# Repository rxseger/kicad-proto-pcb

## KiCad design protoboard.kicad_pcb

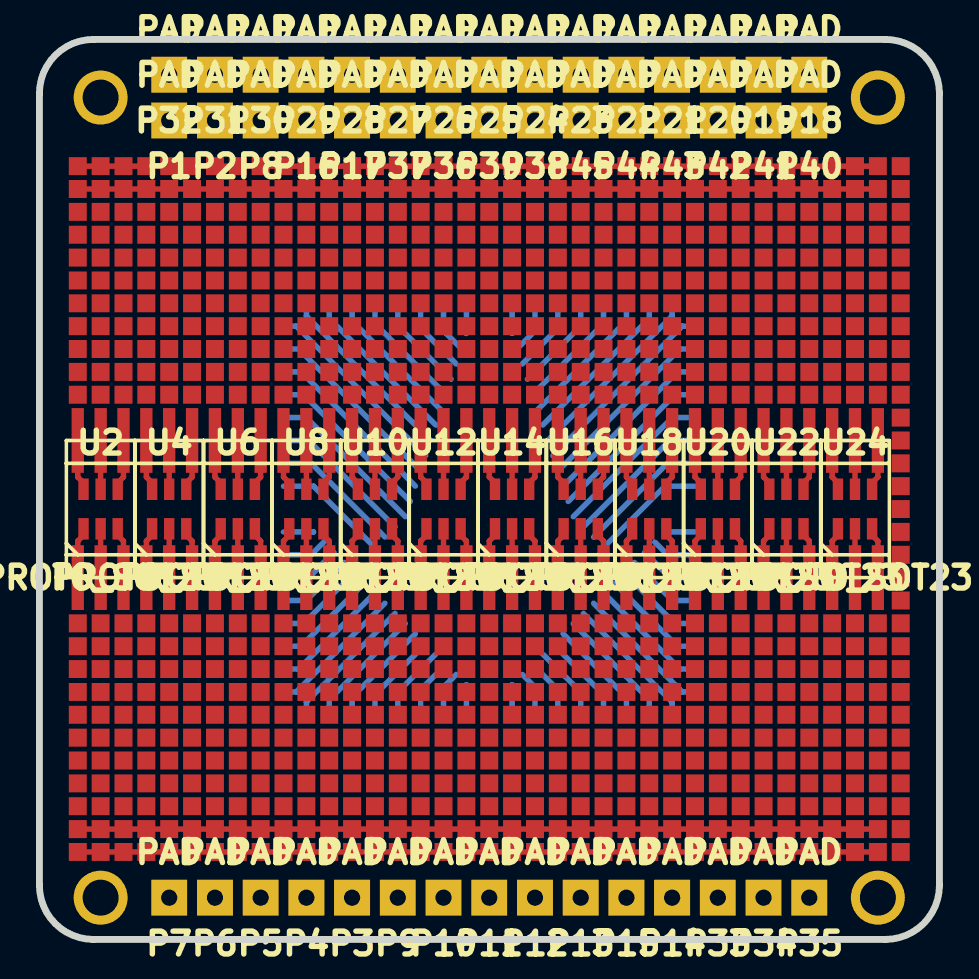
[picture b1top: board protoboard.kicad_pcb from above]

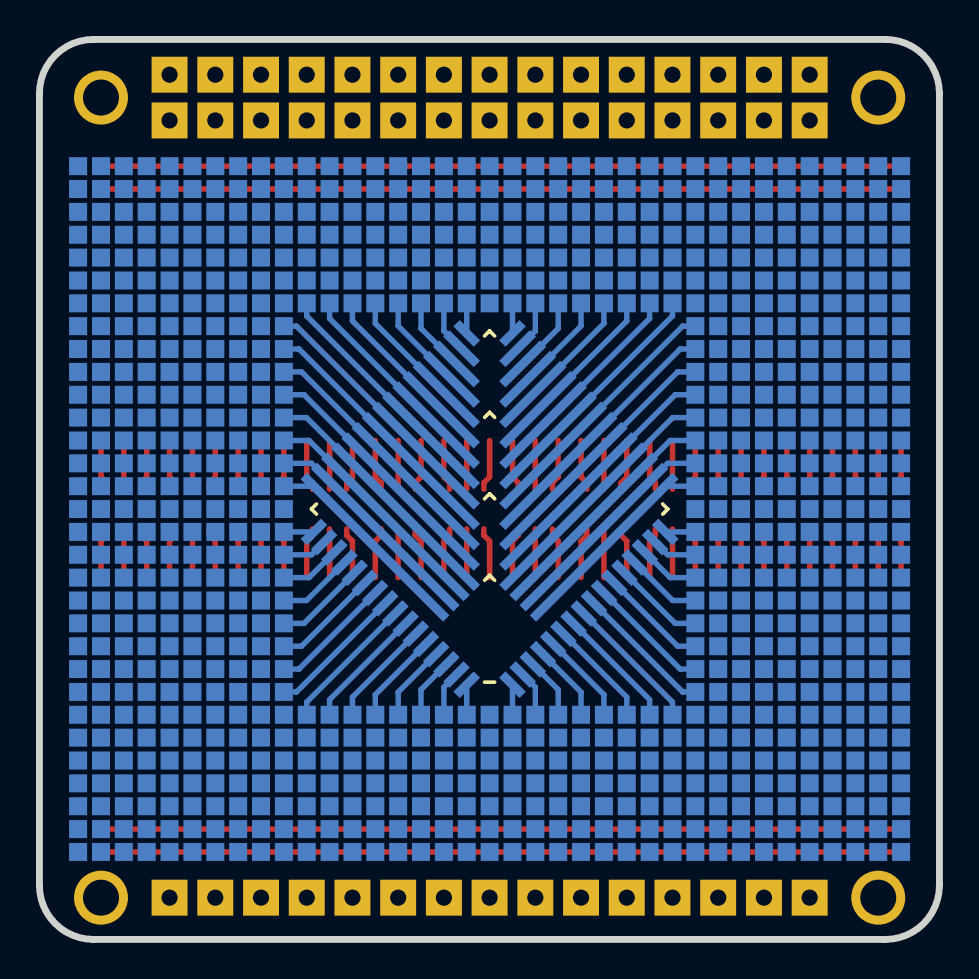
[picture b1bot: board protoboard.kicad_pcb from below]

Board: 2 copper layers, 50.0 x 50.0 mm, 1755 parts (859 on the bottom side), 140 nets.

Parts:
H1, H2, H3, H4: HOLE; hole_2mm
P1, P2, P3, P4, P5, P6, P7, P8, P9, P10, P11, P12, P13, P14, P15, P16, P17, P18, P19, P20, P21, P22, P23, P24, P25, P26, P27, P28, P29, P30, P31, P32, P33, P34, P35, P36, P37, P38, P39, P40, P41, P42, P43, P44, P45: PAD; proto_pad2
PT1, PT2, PT3, PT4, PT5, PT6, PT7, PT8, PT9, PT10, PT11, PT12, PT13, PT14, PT15, PT16, PT17, PT18, PT19, PT20, PT21, PT22, PT23, PT24, PT25, PT26, PT27, PT28, PT29, PT30, PT31, PT32, PT33, PT34, PT35, PT36, PT37, PT38, PT39, PT40, PT41, PT42, PT43, PT44, PT45, PT46, PT47, PT48, PT49, PT50, PT51, PT52, PT53, PT54, PT55, PT56, PT57, PT58, PT59, PT60, PT61, PT62, PT63, PT64: PAD; proto_pad
TQFP1: PROTO_TQFP64; proto_tqfp_08
U1, U3, U5, U7, U9, U11, U13, U15, U17, U19, U21, U23: PROTO_SOIC6; proto_soic6
U2, U4, U6, U8, U10, U12, U14, U16, U18, U20, U22, U24: PROTO_SOT23; proto_sot23
U25, U26, U27, U28, U29, U30, U31, U32, U33, U34, U35, U36, U37, U38, U39, U40, U41, U42, U43, U44, U45, U46, U47, U48, U49, U50, U51, U52, U53, U54, U55, U56, U57, U58, U59, U60, U61, U62, U63, U64, U65, U66, U67, U68, U69, U70, U71, U72, U73, U74, U75, U76, U77, U78, U79, U80, U81, U82, U83, U84, U85, U86, U87, U88, U89, U90, U91, U92, U93, U94, U95, U96, U97, U98, U99, U100, U101, U102, U103, U104, U105, U106, U107, U108, U109, U110, U111, U112, U113, U114, U115, U116, U117, U118, U119, U120, U121, U122, U123, U124, U125, U126, U127, U128, U129, U130, U131, U132, U133, U134, U135, U136, U137, U138, U139, U140, U141, U142, U143, U144, U145, U146, U147, U148, U149, U150, U151, U152, U153, U154, U155, U156, U157, U158, U159, U160, U161, U162, U163, U164, U165, U166, U167, U168, U169, U170, U171, U172, U173, U174, U175, U176, U177, U178, U179, U181, U182, U183, U184, U185, U186, U187, U189, U190, U191, U192, U193, U194, U196, U197, U198, U199, U200, U201, U202, U203, U204, U206, U207, U208, U209, U210, U211, U212, U213, U215, U216, U217, U218, U219, U220, U222, U223, U225, U226, U227, U228, U229, U230, U231, U232, U233, U234, U235, U236, U237, U238, U239, U240, U241, U242, U243, U244, U245, U246, U247, U248, U249, U250, U251, U252, U253, U255, U256, U257, U258, U259, U262, U263, U264, U265, U266, U267, U268, U269, U270, U271, U273, U274, U275, U276, U277, U278, U279, U281, U282, U283, U284, U285, U286, U287, U288, U289, U290, U291, U292, U294, U295, U296, U297, U298, U299, U301, U302, U303, U304, U305, U306, U307, U308, U309, U310, U311, U312, U314, U315, U316, U317, U318, U319, U321, U322, U323, U324, U325, U326, U327, U328, U329, U331, U332, U333, U334, U335, U336, U337, U338, U339, U340, U341, U342, U343, U346, U347, U348, U349, U350, U351, U352, U353, U354, U355, U356, U357, U358, U359, U360, U361, U362, U364, U365, U366, U367, U368, U369, U370, U371, U372, U373, U374, U375, U376, U377, U378, U379, U380, U381, U382, U383, U384, U385, U386, U387, U388, U389, U390, U391, U392, U393, U394, U395, U396, U397, U398, U399, U400, U401, U402, U403, U404, U405, U406, U407, U408, U409, U410, U411, U412, U413, U414, U415, U416, U417, U418, U419, U420, U421, U422, U423, U424, U425, U426, U427, U428, U429, U430, U431, U432, U433, U434, U435, U436, U437, U438, U439, U440, U441, U442, U443, U444, U445, U446, U447, U448, U449, U450, U451, U452, U453, U454, U455, U456, U457, U458, U459, U460, U461, U462, U463, U465, U466, U467, U469, U470, U471, U472, U473, U474, U475, U476, U477, U478, U479, U480, U481, U482, U483, U484, U485, U486, U487, U488, U489, U490, U491, U492, U494, U496, U497, U498, U499, U500, U501, U502, U503, U504, U505, U506, U507, U508, U509, U511, U512, U513, U514, U515, U516, U517, U518, U519, U520, U521, U522, U523, U524, U525, U526, U527, U528, U529, U530, U531, U532, U533, U534, U535, U536, U537, U538, U539, U540, U541, U542, U543, U544, U545, U546, U547, U548, U549, U550, U551, U552, U553, U554, U555, U556, U558, U559, U561, U562, U563, U564, U565, U566, U567, U568, U569, U570, U571, U572, U573, U576, U577, U578, U583, U584, U585, U586, U587, U588, U589, U595, U596, U597, U598, U599, U600, U601, U602, U603, U604, U605, U606, U607, U608, U609, U610, U611, U612, U613, U614, U615, U616, U617, U618, U619, U620, U621, U622, U623, U624, U625, U626, U627, U629, U630, U631, U632, U633, U634, U636, U637, U638, U639, U640, U641, U642, U643, U644, U645, U646, U647, U649, U650, U651, U652, U655, U657, U658, U659, U660, U661, U662, U663, U664, U665, U666, U667, U668, U670, U671, U674, U675, U676, U677, U678, U679, U680, U681, U682, U683, U684, U685, U686, U687, U688, U689, U690, U691, U692, U693, U694, U695, U696, U697, U698, U699, U700, U701, U702, U703, U704, U705, U706, U707, U708, U709, U710, U711, U712, U713, U714, U715, U716, U717, U718, U719, U720, U721, U722, U723, U724, U725, U726, U727, U729, U730, U731, U734, U735, U739, U740, U741, U742, U744, U745, U747, U748, U749, U750, U752, U753, U754, U755, U758, U759, U760, U763, U764, U765, U766, U767, U768, U769, U770, U771, U773, U774, U777, U778, U779, U780, U781, U782, U783, U785, U786, U787, U788, U790, U791, U794, U795, U796, U797, U798, U799, U800, U801, U802, U803, U804, U805, U806, U808, U809, U811, U812, U813, U814, U815, U816, U817, U818, U819, U820, U821, U822, U823, U825, U826, U828, U829, U830, U831, U832, U833, U834, U836, U837, U839, U840, U841, U842, U843, U844, U845, U846, U847, U848, U849, U851, U853, U854, U855, U856, U857, U859, U860, U861, U862, U864, U865, U866, U867, U868, U869, U870, U871, U872, U873, U874, U875, U876, U877, U878, U879, U880, U881, U882, U883, U884, U885, U886, U887, U888, U889, U890, U891, U892, U893, U894, U895, U896, U897, U898, U899, U900, U901, U902, U903, U904, U905, U906, U907, U908, U909, U910, U911, U912, U913, U914, U915, U916, U917, U918, U919, U920, U921, U922, U923, U924, U925, U926, U927, U928, U929, U930, U931, U932, U933, U934, U935, U936, U937, U938, U939, U940, U941, U942, U943, U944, U945, U946, U947, U948, U949, U950, U951, U952, U953, U954, U955, U956, U957, U958, U959, U960, U961, U962, U963, U964, U965, U966, U967, U968, U969, U970, U971, U972, U973, U974, U975, U976, U977, U978, U979, U980, U981, U982, U983, U984, U985, U986, U987, U988, U989, U990, U991, U992, U993, U994, U995, U996, U997, U998, U999, U1000, U1001, U1002, U1003, U1004, U1005, U1006, U1007, U1008, U1009, U1010, U1011, U1012, U1013, U1014, U1015, U1016, U1017, U1018, U1019, U1020, U1021, U1022, U1023, U1024, U1025, U1026, U1027, U1028, U1029, U1030, U1031, U1032, U1033, U1034, U1035, U1036, U1037, U1038, U1039, U1040, U1041, U1042, U1043, U1044, U1045, U1046, U1047, U1048, U1049, U1050, U1051, U1052, U1053, U1054, U1055, U1056, U1057, U1058, U1059, U1060, U1061, U1062, U1063, U1064, U1065, U1066, U1067, U1068, U1069, U1070, U1071, U1072, U1073, U1074, U1075, U1076, U1077, U1078, U1079, U1080, U1081, U1082, U1083, U1084, U1085, U1086, U1087, U1088, U1089, U1090, U1091, U1092, U1093, U1094, U1095, U1096, U1097, U1098, U1099, U1100, U1101, U1102, U1103, U1104, U1105, U1106, U1108, U1110, U1111, U1112, U1113, U1114, U1115, U1116, U1117, U1118, U1119, U1120, U1121, U1122, U1123, U1124, U1125, U1126, U1127, U1128, U1129, U1130, U1131, U1132, U1133, U1134, U1135, U1136, U1137, U1138, U1139, U1140, U1141, U1142, U1143, U1144, U1145, U1146, U1147, U1148, U1149, U1150, U1151, U1152, U1153, U1154, U1155, U1156, U1157, U1158, U1159, U1160, U1161, U1162, U1163, U1164, U1165, U1166, U1167, U1168, U1169, U1170, U1171, U1172, U1173, U1174, U1175, U1176, U1177, U1178, U1179, U1180, U1181, U1182, U1183, U1184, U1185, U1186, U1187, U1188, U1189, U1190, U1191, U1192, U1193, U1194, U1195, U1196, U1197, U1198, U1199, U1200, U1201, U1202, U1203, U1204, U1205, U1206, U1207, U1208, U1209, U1210, U1211, U1212, U1213, U1214, U1215, U1216, U1217, U1218, U1219, U1220, U1221, U1222, U1223, U1224, U1225, U1226, U1227, U1228, U1229, U1230, U1231, U1232, U1233, U1234, U1235, U1236, U1237, U1238, U1239, U1240, U1241, U1242, U1243, U1244, U1245, U1246, U1247, U1248, U1249, U1250, U1251, U1252, U1253, U1254, U1255, U1256, U1257, U1258, U1259, U1260, U1261, U1262, U1263, U1264, U1265, U1266, U1267, U1268, U1269, U1270, U1271, U1272, U1273, U1274, U1275, U1276, U1277, U1278, U1279, U1280, U1281, U1282, U1283, U1284, U1285, U1286, U1287, U1288, U1289, U1290, U1291, U1292, U1293, U1294, U1295, U1296, U1297, U1299, U1300, U1301, U1302, U1303, U1304, U1306, U1307, U1308, U1309, U1310, U1311, U1313, U1314, U1315, U1316, U1317, U1318, U1319, U1320, U1322, U1323, U1324, U1325, U1326, U1329, U1330, U1331, U1332, U1333, U1334, U1335, U1336, U1337, U1338, U1341, U1342, U1343, U1344, U1345, U1348, U1349, U1352, U1353, U1354, U1355, U1356, U1357, U1358, U1361, U1362, U1364, U1367, U1368, U1369, U1370, U1371, U1372, U1373, U1374, U1375, U1376, U1379, U1380, U1384, U1385, U1386, U1387, U1388, U1390, U1391, U1394, U1396, U1397, U1398, U1399, U1400, U1401, U1402, U1403, U1406, U1409, U1410, U1411, U1412, U1414, U1416, U1417, U1418, U1419, U1420, U1421, U1422, U1423, U1424, U1425, U1426, U1427, U1430, U1435, U1436, U1437, U1438, U1439, U1440, U1441, U1442, U1443, U1444, U1445, U1446, U1447, U1448, U1449, U1450, U1451, U1452, U1453, U1455, U1456, U1457, U1460, U1461, U1462, U1467, U1470, U1471, U1481, U1482, U1483, U1484, U1485, U1486, U1487, U1488, U1489, U1490, U1491, U1492, U1493, U1494, U1495, U1496, U1497, U1498, U1499, U1500, U1501, U1502, U1503, U1504, U1505, U1506, U1507, U1508, U1509, U1510, U1511, U1512, U1513, U1514, U1515, U1516, U1517, U1518, U1519, U1520, U1521, U1522, U1523, U1524, U1525, U1526, U1527, U1528, U1529, U1530, U1531, U1532, U1533, U1534, U1535, U1536, U1537, U1538, U1539, U1540, U1541, U1542, U1543, U1544, U1545, U1546, U1547, U1548, U1549, U1550, U1551, U1552, U1553, U1554, U1555, U1556, U1557, U1558, U1559, U1560, U1561, U1562, U1563, U1564, U1565, U1566, U1567, U1568, U1569, U1570, U1571, U1572, U1573, U1574, U1575, U1576, U1577, U1578, U1579, U1580, U1581, U1582, U1583, U1584, U1585, U1586, U1587, U1588, U1589, U1590, U1591, U1592, U1593, U1594, U1595, U1596, U1597, U1598, U1599, U1600, U1601, U1602, U1603, U1604, U1605, U1606, U1607, U1608, U1609, U1610, U1611, U1612, U1613, U1614, U1615, U1616, U1617, U1618, U1619, U1620, U1621, U1622, U1623, U1624, U1625, U1626, U1627, U1628, U1629, U1630, U1631, U1632, U1633, U1634, U1635, U1636, U1637, U1638, U1639, U1640, U1641, U1642, U1643, U1644, U1646, U1647, U1648, U1649, U1650, U1651, U1652, U1653, U1655, U1656, U1657, U1658, U1659, U1660, U1661, U1662, U1663, U1664, U1665, U1666, U1667, U1668, U1669, U1671, U1672, U1674, U1675, U1676, U1677, U1679, U1680, U1681, U1682, U1683, U1684, U1685, U1686, U1687, U1688, U1689, U1690, U1691, U1692, U1693, U1694, U1695, U1698, U1699, U1700, U1701, U1702, U1703, U1704, U1705, U1706, U1707, U1708, U1709, U1710, U1711, U1712, U1713, U1714, U1715, U1716, U1717, U1718, U1719, U1721, U1723, U1724, U1725, U1726, U1727, U1728, U1729, U1731, U1732, U1733, U1734, U1735, U1736, U1737, U1738, U1739, U1740, U1741, U1743, U1744, U1745, U1746, U1747, U1748, U1749, U1750, U1751, U1752, U1754, U1756, U1757, U1758, U1759, U1760, U1761, U1762, U1763, U1765, U1767, U1772, U1773, U1774, U1775, U1776, U1777, U1778, U1779, U1780, U1781, U1782, U1783, U1784, U1785, U1786, U1787, U1788, U1789, U1790, U1791, U1792, U1793, U1794, U1795: PAD; proto_pad

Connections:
unnamed: PT18.1, TQFP1.18
unnamed: PT19.1, TQFP1.19
unnamed: PT49.1, TQFP1.49
unnamed: PT57.1, TQFP1.57
unnamed: PT58.1, TQFP1.58
unnamed: PT59.1, TQFP1.59
unnamed: PT28.1, TQFP1.28
unnamed: PT29.1, TQFP1.29
unnamed: PT47.1, TQFP1.47
unnamed: PT48.1, TQFP1.48
unnamed: PT37.1, TQFP1.37
unnamed: PT38.1, TQFP1.38
unnamed: PT39.1, TQFP1.39
unnamed: PT6.1, TQFP1.6
unnamed: U1.4, U2.4
unnamed: U1.6, U2.6
unnamed: PT1.1, TQFP1.1
unnamed: PT2.1, TQFP1.2
unnamed: PT3.1, TQFP1.3
unnamed: PT4.1, TQFP1.4
unnamed: PT5.1, TQFP1.5
unnamed: U1.2, U2.2
unnamed: PT7.1, TQFP1.7
unnamed: PT8.1, TQFP1.8
unnamed: PT9.1, TQFP1.9
unnamed: PT10.1, TQFP1.10
unnamed: PT20.1, TQFP1.20
unnamed: PT30.1, TQFP1.30
unnamed: PT40.1, TQFP1.40
unnamed: PT50.1, TQFP1.50
unnamed: U3.3, U4.3
unnamed: U3.5, U4.5
unnamed: U3.2, U4.2
unnamed: U3.4, U4.4
unnamed: U3.6, U4.6
unnamed: U1.1, U2.1
unnamed: U1.3, U2.3
unnamed: U1.5, U2.5
unnamed: PT45.1, TQFP1.45
unnamed: PT14.1, TQFP1.14
unnamed: PT24.1, TQFP1.24
unnamed: PT34.1, TQFP1.34
unnamed: PT44.1, TQFP1.44
unnamed: PT54.1, TQFP1.54
unnamed: PT64.1, TQFP1.64
unnamed: PT15.1, TQFP1.15
unnamed: PT25.1, TQFP1.25
unnamed: PT35.1, TQFP1.35
unnamed: PT63.1, TQFP1.63
unnamed: PT55.1, TQFP1.55
unnamed: PT26.1, TQFP1.26
unnamed: PT36.1, TQFP1.36
unnamed: PT46.1, TQFP1.46
unnamed: PT56.1, TQFP1.56
unnamed: PT17.1, TQFP1.17
unnamed: PT27.1, TQFP1.27
unnamed: PT32.1, TQFP1.32
unnamed: PT11.1, TQFP1.11
unnamed: PT21.1, TQFP1.21
unnamed: PT31.1, TQFP1.31
unnamed: PT41.1, TQFP1.41
unnamed: PT51.1, TQFP1.51
unnamed: PT12.1, TQFP1.12
unnamed: PT22.1, TQFP1.22
unnamed: PT60.1, TQFP1.60
unnamed: PT42.1, TQFP1.42
unnamed: PT52.1, TQFP1.52
unnamed: PT62.1, TQFP1.62
unnamed: PT13.1, TQFP1.13
unnamed: PT23.1, TQFP1.23
unnamed: PT33.1, TQFP1.33
unnamed: PT43.1, TQFP1.43
unnamed: PT53.1, TQFP1.53
unnamed: PT61.1, TQFP1.61
unnamed: PT16.1, TQFP1.16
unnamed: U66.1, U67.1, U68.1, U69.1, U70.1, U71.1, U72.1, U73.1, U74.1, U75.1, U76.1, U77.1, U78.1, U79.1, U80.1, U81.1, U82.1, U83.1, U84.1, U85.1, U86.1, U87.1, U88.1, U89.1, U90.1, U91.1, U92.1, U93.1, U94.1, U95.1, U96.1, U97.1, U98.1, U99.1, U100.1, U101.1
unnamed: U25.1, U26.1, U27.1, U28.1, U29.1, U102.1, U103.1, U104.1, U105.1, U106.1, U107.1, U108.1, U109.1, U110.1, U111.1, U112.1, U113.1, U114.1, U115.1, U116.1, U117.1, U118.1, U119.1, U120.1, U121.1, U122.1, U123.1, U124.1, U125.1, U126.1, U127.1, U128.1, U129.1, U130.1, U131.1, U132.1
unnamed: U133.1, U134.1, U135.1, U136.1, U137.1, U138.1, U139.1, U140.1, U141.1, U142.1, U143.1, U144.1, U145.1, U146.1, U147.1, U148.1, U149.1, U150.1, U151.1, U152.1, U153.1, U154.1, U155.1, U156.1, U157.1, U158.1, U159.1, U160.1, U161.1, U162.1, U163.1, U164.1, U165.1, U166.1, U167.1, U168.1
unnamed: U13.2, U14.2
unnamed: U13.4, U14.4
unnamed: U13.6, U14.6
unnamed: U11.1, U12.1
unnamed: U11.3, U12.3
unnamed: U11.4, U12.4
unnamed: U11.5, U12.5
unnamed: U11.6, U12.6
unnamed: U15.1, U16.1
unnamed: U15.3, U16.3
unnamed: U15.5, U16.5
unnamed: U15.2, U16.2
unnamed: U15.4, U16.4
unnamed: U15.6, U16.6
unnamed: U13.1, U14.1
unnamed: U13.3, U14.3
unnamed: U13.5, U14.5
unnamed: U5.5, U6.5
unnamed: U7.2, U8.2
unnamed: U7.4, U8.4
unnamed: U7.6, U8.6
unnamed: U5.1, U6.1
unnamed: U5.3, U6.3
unnamed: U5.2, U6.2
unnamed: U5.4, U6.4
unnamed: U5.6, U6.6
unnamed: U3.1, U4.1
unnamed: U9.3, U10.3
unnamed: U9.4, U10.4
unnamed: U9.5, U10.5
unnamed: U9.2, U10.2
unnamed: U17.6, U18.6
unnamed: U9.6, U10.6
unnamed: U7.1, U8.1
unnamed: U7.3, U8.3
unnamed: U30.1, U31.1, U32.1, U33.1, U34.1, U35.1, U36.1, U37.1, U38.1, U39.1, U40.1, U41.1, U42.1, U43.1, U44.1, U45.1, U46.1, U47.1, U48.1, U49.1, U50.1, U51.1, U52.1, U53.1, U54.1, U55.1, U56.1, U57.1, U58.1, U59.1, U60.1, U61.1, U62.1, U63.1, U64.1, U65.1
unnamed: U23.3, U24.3
unnamed: U23.5, U24.5
unnamed: U23.2, U24.2
unnamed: U23.4, U24.4
unnamed: U17.3, U18.3
unnamed: U19.2, U20.2
unnamed: U19.4, U20.4
unnamed: U19.6, U20.6
unnamed: U17.1, U18.1
unnamed: U19.5, U20.5
unnamed: U17.5, U18.5
unnamed: U17.2, U18.2
unnamed: U17.4, U18.4
unnamed: U23.6, U24.6
unnamed: U21.1, U22.1
unnamed: U21.3, U22.3
unnamed: U21.4, U22.4
unnamed: U21.6, U22.6
unnamed: U19.1, U20.1
unnamed: U19.3, U20.3
unnamed: U11.2, U12.2
unnamed: U9.1, U10.1
unnamed: U7.5, U8.5
unnamed: U21.2, U22.2
unnamed: U21.5, U22.5
unnamed: U23.1, U24.1

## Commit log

2016-10-23 Add curved board outline
2016-10-23 Position board within curved edge cuts
2016-10-23 Regenerate gerbers (.drl -> .txt, .gm1 -> .gko)
2016-10-23 Update png previews, new curved outline
